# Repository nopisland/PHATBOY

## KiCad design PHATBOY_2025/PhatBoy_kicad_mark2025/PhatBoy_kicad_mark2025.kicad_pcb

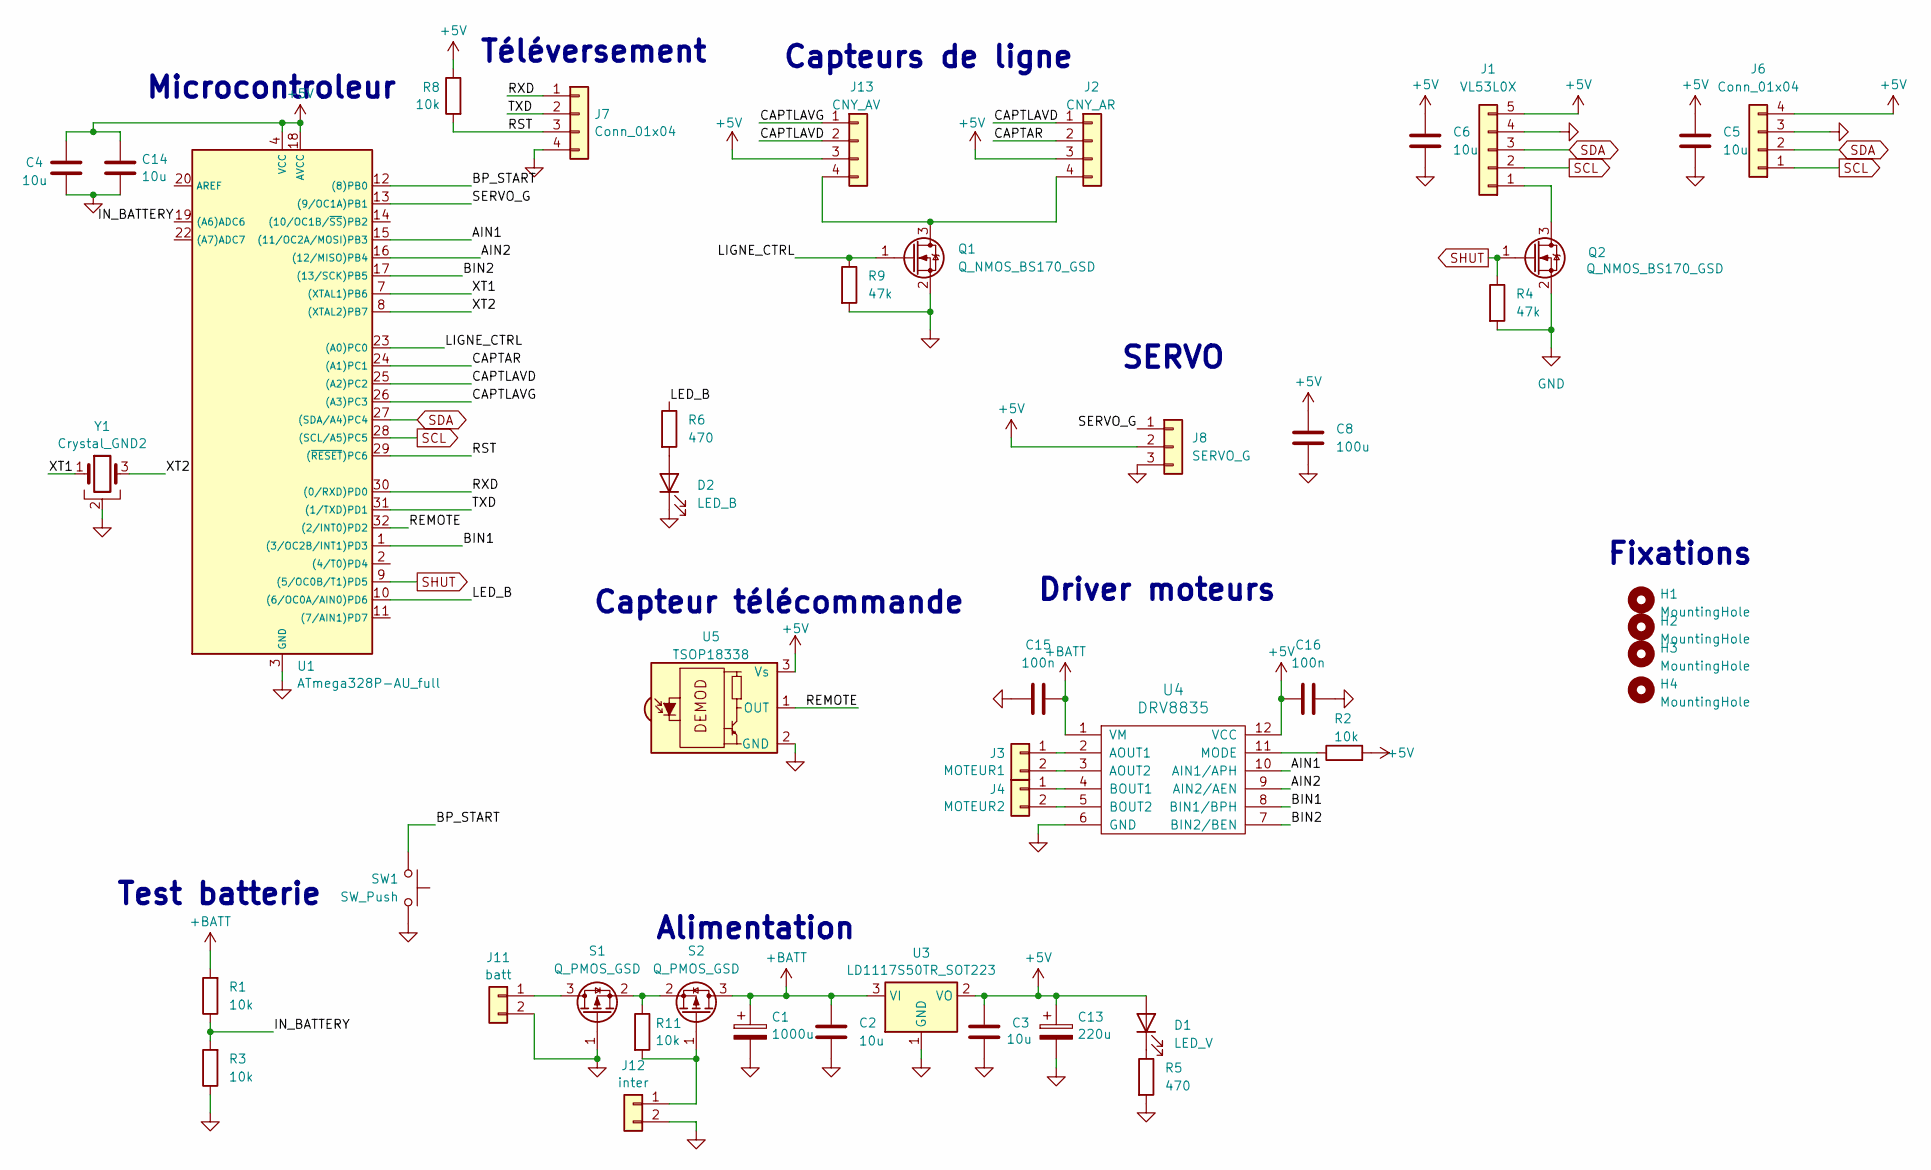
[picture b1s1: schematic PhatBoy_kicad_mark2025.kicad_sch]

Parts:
C1: 1000u; CP_Elec_10x10
C2: 10u; C_0603_1608Metric
C3, C4, C5, C6, C14: 10u; C_1206_3216Metric
C8: 100u; C_1206_3216Metric
C13: 220u; C_1206_3216Metric
C15, C16: 100n; C_0603_1608Metric
D1: LED_V; LED_1206_3216Metric
D2: LED_B; LED_1206_3216Metric
H1, H2, H3, H4: MountingHole; MountingHole_3.2mm_M3_DIN965_Pad
J1: VL53L0X; PinHeader_1x05_P2.54mm_Horizontal
J2: CNY_AR; GROVE_HY2.0_VERTICAL_SMD
J3: MOTEUR1; PinHeader_1x02_P2.54mm_Horizontal
J4: MOTEUR2; PinHeader_1x02_P2.54mm_Horizontal
J6: Conn_01x04; PinHeader_1x04_P2.54mm_Horizontal
J7: Conn_01x04; PinSocket_1x04_P2.54mm_Vertical
J8: SERVO_G; PinHeader_1x03_P2.54mm_Horizontal
J11: batt; PinHeader_1x02_P2.54mm_Horizontal
J12: inter; PinHeader_1x02_P2.54mm_Horizontal
J13: CNY_AV; GROVE_HY2.0_VERTICAL_SMD
Q1, Q2: Q_NMOS_BS170_GSD; TSOT-23
R1, R3: 10k; C_0603_1608Metric
R2, R8, R11: 10k; R_0603_1608Metric
R4, R9: 47k; C_0603_1608Metric
R5, R6: 470; R_0603_1608Metric
S1, S2: Q_PMOS_GSD; TSOT-23
SW1: SW_Push; BP_Schruter_LSH
U1: ATmega328P-AU_full; TQFP32m
U3: LD1117S50TR_SOT223; SOT-223-3_TabPin2
U4: DRV8835; WSON-12
U5: TSOP18338; Vishay_MOLD-3Pin
Y1: Crystal_GND2; osc_CSTNE

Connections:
+5V: C3.1, C4.1, C5.1, C6.1, C8.1, C13.1, C14.1, C16.1, D1.2 (A), J1.5, J2.3, J6.4, J8.2, J13.3, R2.2, R8.1, U1.4 (VCC), U1.6 (VCC), U1.18 (AVCC), U3.2 (VO), U4.12 (VCC), U5.3 (Vs)
+BATT: C1.1, C2.1, C15.2, R1.2, S2.3 (D), U3.3 (VI), U4.1 (VM)
/AIN1: U1.15 ((11/OC2A/MOSI)PB3), U4.10 (AIN1/APH)
/AIN2: U1.16 ((12/MISO)PB4), U4.9 (AIN2/AEN)
/BIN1: U1.1 ((3/OC2B/INT1)PD3), U4.8 (BIN1/BPH)
/BIN2: U1.17 ((13/SCK)PB5), U4.7 (BIN2/BEN)
/BP_START: SW1.2, U1.12 ((8)PB0)
/CAPTAR: J2.2, U1.24 ((A1)PC1)
/CAPTLAVD: J2.1, J13.2, U1.25 ((A2)PC2)
/CAPTLAVG: J13.1, U1.26 ((A3)PC3)
/IN_BATTERY: R1.1, R3.2, U1.19 ((A6)ADC6)
/LED_B: R6.1, U1.10 ((6/OC0A/AIN0)PD6)
/LIGNE_CTRL: Q1.1 (G), R9.1, U1.23 ((A0)PC0)
/REMOTE: U1.32 ((2/INT0)PD2), U5.1 (OUT)
/RST: J7.3, R8.2, U1.29 ((~RESET)PC6)
/RXD: J7.1, U1.30 ((0/RXD)PD0)
/SERVO_G: J8.1, U1.13 ((9/OC1A)PB1)
/TXD: J7.2, U1.31 ((1/TXD)PD1)
/XT1: U1.7 ((XTAL1)PB6), Y1.1
/XT2: U1.8 ((XTAL2)PB7), Y1.3
GND: C1.2, C2.2, C3.2, C4.2, C5.2, C6.2, C8.2, C13.2, C14.2, C15.1, C16.2, D2.1 (K), J1.4, J6.3, J7.4, J8.3, J11.2, J12.2, Q1.2 (S), Q2.2 (S), R3.1, R4.2, R5.2, R9.2, S1.1 (G), SW1.1, U1.3 (GND), U1.5 (GND), U1.21 (GND), U3.1 (GND), U4.6 (GND), U5.2 (GND), Y1.2
unnamed: D1.1 (K), R5.1
unnamed: D2.2 (A), R6.2
unnamed: J1.1, Q2.3 (D)
unnamed: J3.1, U4.2 (AOUT1)
unnamed: J3.2, U4.3 (AOUT2)
unnamed: J4.1, U4.4 (BOUT1)
unnamed: J4.2, U4.5 (BOUT2)
unnamed: J11.1, S1.3 (D)
unnamed: J12.1, R11.2, S2.1 (G)
unnamed: J2.4, J13.4, Q1.3 (D)
unnamed: R11.1, S1.2 (S), S2.2 (S)
unnamed: R2.1, U4.11 (MODE)
SCL: J1.2, J6.1, U1.28 ((SCL/A5)PC5)
SDA: J1.3, J6.2, U1.27 ((SDA/A4)PC4)
SHUT: Q2.1 (G), R4.1, U1.9 ((5/OC0B/T1)PD5)

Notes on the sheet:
Microcontroleur
Fixations
Téléversement
Capteur télécommande
Test batterie
Alimentation
SERVO
Driver moteurs
Capteurs de ligne

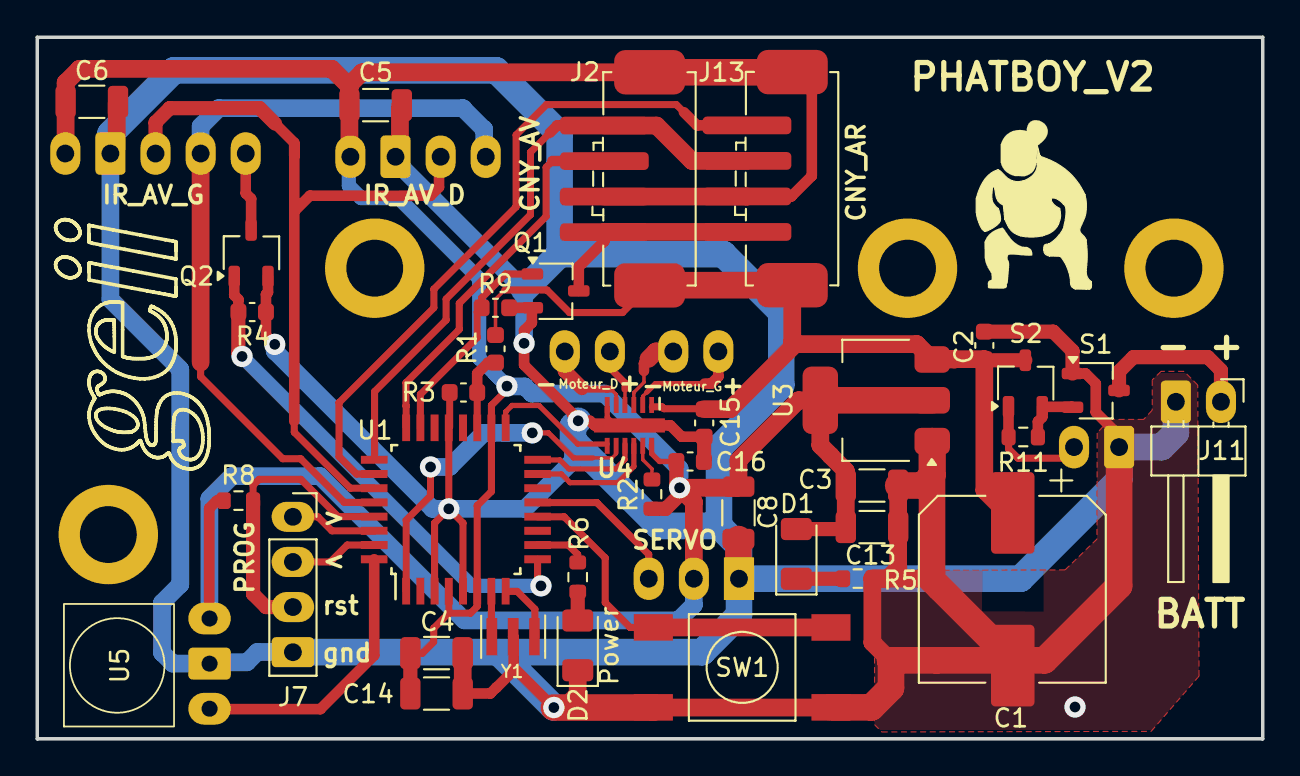
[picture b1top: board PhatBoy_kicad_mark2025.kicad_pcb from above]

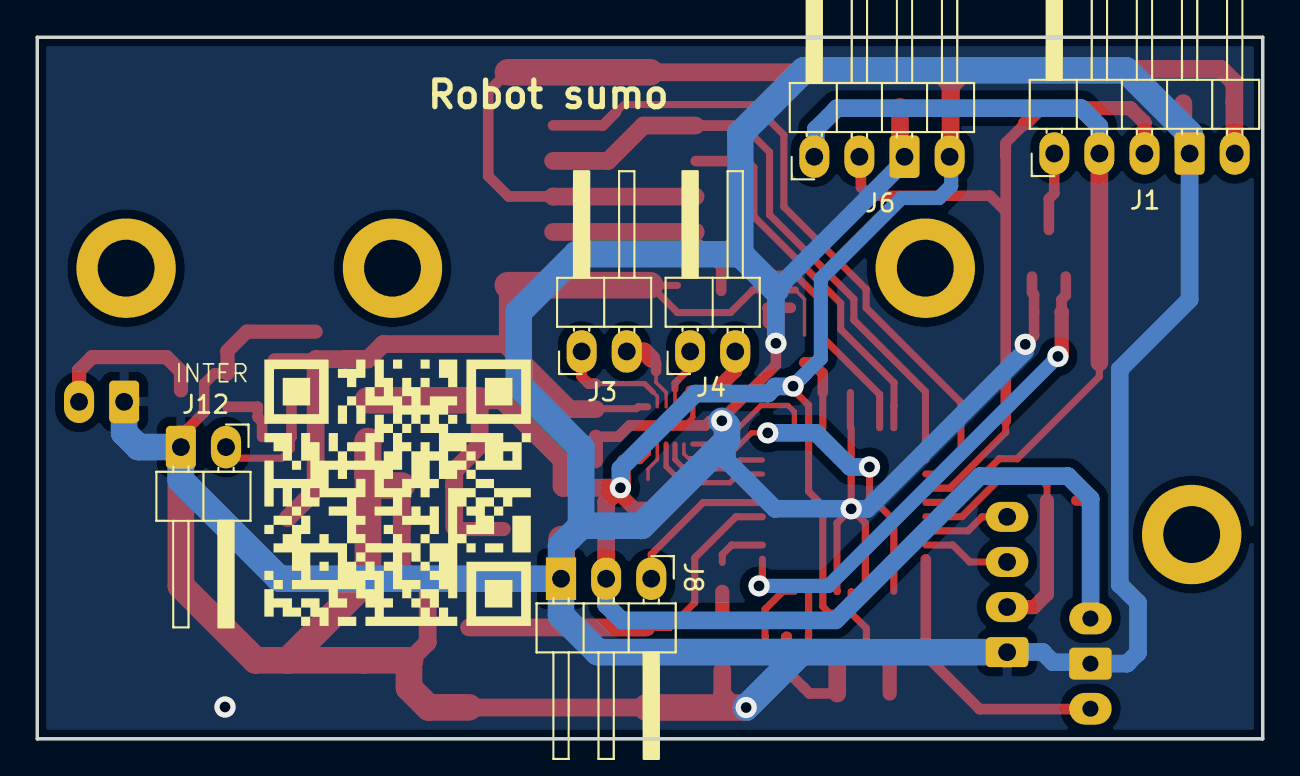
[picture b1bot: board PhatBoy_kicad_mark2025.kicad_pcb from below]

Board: 2 copper layers, 69.0 x 39.5 mm, 47 parts (6 on the bottom side), 36 nets.

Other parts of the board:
Ref**: Val**; logo_geii_fsilk

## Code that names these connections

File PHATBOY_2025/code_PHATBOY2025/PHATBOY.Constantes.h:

#ifdef PhatboyBlue
#define POSCLOSE         20
#define POSOPEN          0
#endif


#ifdef PhatboyViolet
#define POSCLOSE         0
#define POSOPEN          20

#endif 

#define MINWHITEVALUE    200
#define MAXDISTVALUE     350
#define MAXFULLPOWER     70
#define MINBATTERYVALUE  7.4

#define WAITTIME         5000
//#define WAITTIME         3000

#define BACKTIME         900
#define TIMEOUT          100
#define FOCUSTIME        400
#define MAXDISTDIFF      42

/*----------------------------------------
              Acquisition
----------------------------------------*/

#define OUT_NMOS    A0
#define IN_BATTERY  A6
#define IN_BTN      8
#define IN_IRBACK   A1  //CAPTAR
#define IN_IRRIGHT  A2  //CAPTLAVD
#define IN_IRLEFT   A3  //CAPTLAVG
#define XSHUT       5
#define remote      2
#define SDA         A4
#define SCL         A5

/*----------------------------------------
                  Action
----------------------------------------*/
#define LED_B 6
#define OUT_PWM0   12 //AIN2 // PWM
#define OUT_PWM1   11 //AIN1
#define OUT_PWM2   13  //BIN2 // PWM
#define OUT_PWM3   3  //BIN1

#define OUT_SERVO  9





const unsigned long HEADER_ON_MIN  = 8000;
const unsigned long HEADER_ON_MAX  = 10000;
const unsigned long HEADER_OFF_MIN = 4000;
const unsigned long HEADER_OFF_MAX = 5000;

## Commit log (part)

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2026-01-16 ajout du QR_code
2026-01-16 modification de la sériegraphie
2026-01-22 création de fichier gerber
2026-03-27 changement code déclanchement télécomande
2026-04-01 suppression du démarrage avec le pb poussoir
